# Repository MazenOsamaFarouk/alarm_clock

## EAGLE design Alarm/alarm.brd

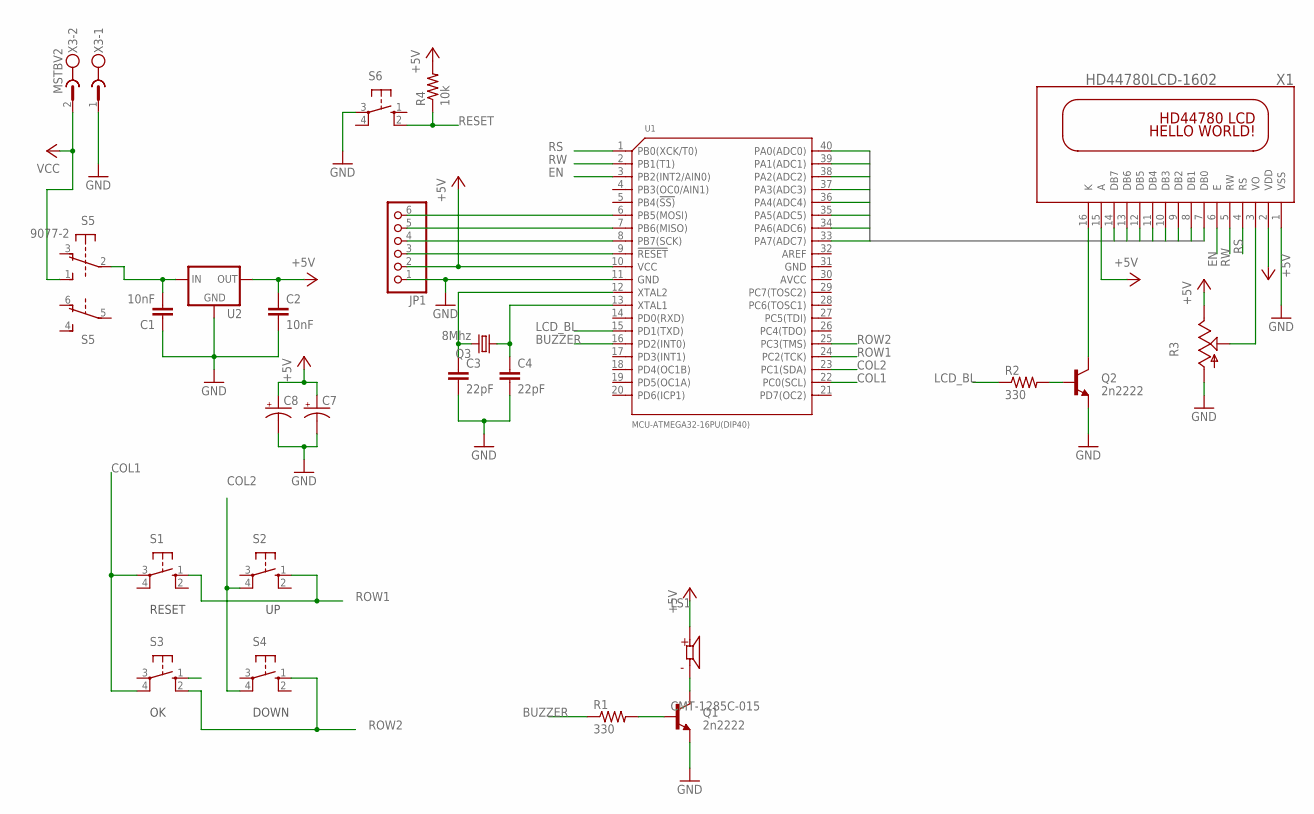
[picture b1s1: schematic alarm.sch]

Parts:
C1, C2: 10nF; C025-025X050
C3, C4: 22pF; C025-025X050
C7, C8: CPOL-USE2.5-6; E2,5-6
JP1: PINHD-1X6; 1X06
LS1: CMT-1285C-015; CUI_CMT-1285C-015
Q1, Q2: 2n2222; TO-92
Q3: 8Mhz; HC49/S
R1, R2: 330; 0207/10
R3: TRIM_US-RS3; RS3
R4: 10k; 0207/10
S1, S2, S3, S4, S6: 10-XX; B3F-10XX
S5: 9077-2
U1: MCU-ATMEGA32-16PU(DIP40); DIP40-2.54-52.3X15.24MM
U2: 78XXL
X1: HD44780LCD-1602; LCD1602
X3: MSTBV2

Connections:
+5V: C2.1, C7.+, C8.+, JP1.2, LS1.P, R3.E, R4.2, U1.10 (VCC), U2.OUT, X1.2 (VDD), X1.15 (A)
BUZZER: R1.1, U1.16 (PD2(INT0))
COL1: S1.3, S3.4 (P1), U1.22 (PC0(SCL))
COL2: S2.4 (P1), S4.4 (P1), U1.23 (PC1(SDA))
EN: U1.3 (PB2(INT2/AIN0)), X1.6 (E)
GND: C1.1, C2.2, C3.2, C4.2, C7.-, C8.-, JP1.1, Q1.3 (E), Q2.3 (E), R3.A, S6.3, U1.11 (GND), U2.GND, X1.1 (VSS), X3.1
LCD_BL: R2.1, U1.15 (PD1(TXD))
unnamed: C1.2, S5.2, U2.IN
unnamed: Q1.2 (B), R1.2
unnamed: LS1.N, Q1.1 (C)
unnamed: C3.1, Q3.2, U1.12 (XTAL2)
unnamed: C4.1, Q3.1, U1.13 (XTAL1)
unnamed: JP1.4, U1.8 (PB7(SCK))
unnamed: JP1.5, U1.7 (PB6(MISO))
unnamed: JP1.6, U1.6 (PB5(MOSI))
unnamed: Q2.1 (C), X1.16 (K)
unnamed: Q2.2 (B), R2.2
unnamed: R3.S, X1.3 (VO)
PA0: U1.40 (PA0(ADC0)), X1.7 (DB0)
PA1: U1.39 (PA1(ADC1)), X1.8 (DB1)
PA2: U1.38 (PA2(ADC2)), X1.9 (DB2)
PA3: U1.37 (PA3(ADC3)), X1.10 (DB3)
PA4: U1.36 (PA4(ADC4)), X1.11 (DB4)
PA5: U1.35 (PA5(ADC5)), X1.12 (DB5)
PA6: U1.34 (PA6(ADC6)), X1.13 (DB6)
PA7: U1.33 (PA7(ADC7)), X1.14 (DB7)
RESET: JP1.3, R4.1, S6.2 (S1), U1.9 (!RESET)
ROW1: S1.1 (S), S2.1 (S), U1.24 (PC2(TCK))
ROW2: S3.2 (S1), S4.1 (S), U1.25 (PC3(TMS))
RS: U1.1 (PB0(XCK/T0)), X1.4 (RS)
RW: U1.2 (PB1(T1)), X1.5 (RW)
VCC: S5.1 (S), X3.2

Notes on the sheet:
RESET
DOWN

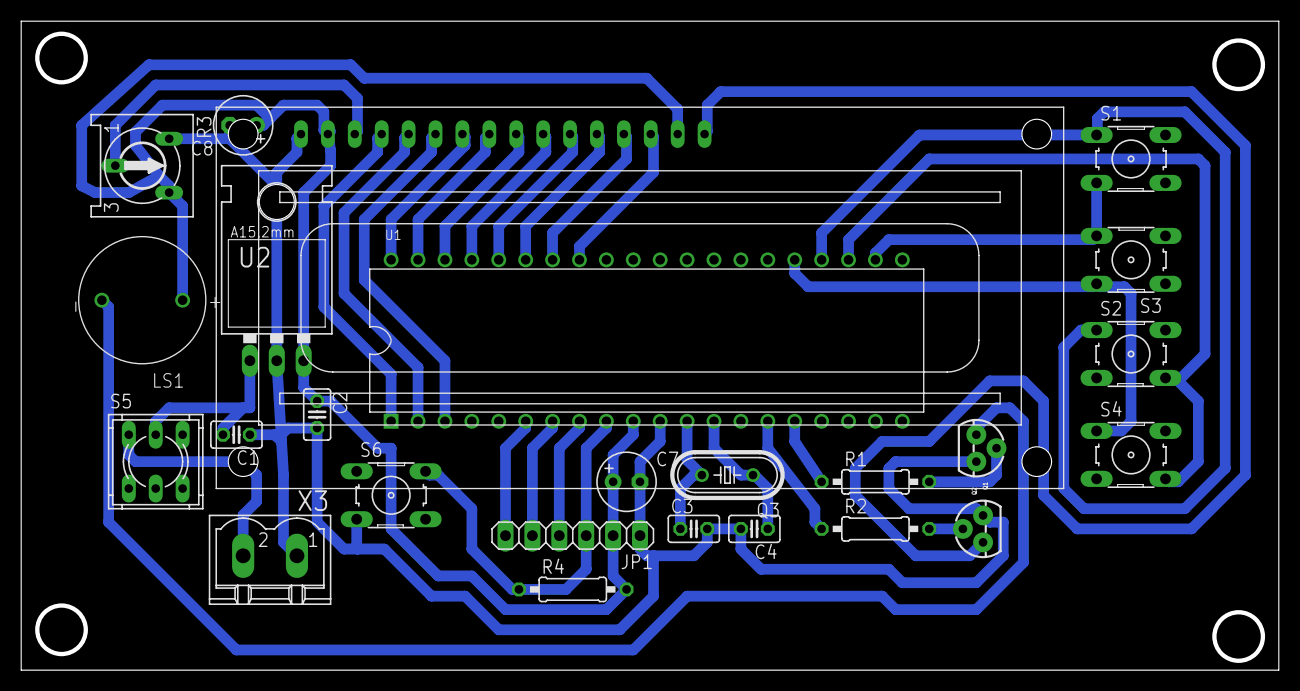
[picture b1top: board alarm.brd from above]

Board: 2 copper layers, 118.7 x 61.3 mm, 25 parts (0 on the bottom side), 32 nets.

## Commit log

2021-03-20 created git repo for the project
2021-03-20 removed old timers library
2021-03-20 added new timers library
2021-03-20 main application structure and includes
2021-03-20 small edits for Timer2
2021-03-20 git ignore
2021-03-20 removed cursor blink
2021-03-20 WARNING: changes made for ATmega16 in ISR __vector_
2021-03-21 added Keypad library instead of buttons
2021-03-21 changed config of LCD to portB and PORTA
2021-03-22 minor edits in timers
2021-03-25 added alarm clock pcb files
2021-03-25 added LCD display on/off control macros
2021-03-25 final commit to main
2021-03-25 eclipse project file changes
2023-01-11 added osama to name
2023-01-11 branch test_8 added its comment in main.c
2023-01-11 branch test_10 added its comment in main.c
2023-01-11 branch test_5 added its comment in main.c
2023-01-11 branch test_2 added its comment in main.c
2023-01-11 branch test_9 added its comment in main.c
2023-01-11 branch test_3 added its comment in main.c
2023-01-11 branch test_6 added its comment in main.c
2023-01-11 branch test_1 added its comment in main.c
2023-01-11 branch test_7 added its comment in main.c
2023-01-11 branch test_4 added its comment in main.c

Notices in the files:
parts and their libraries:
SparkFun-DiscreteSemi: Licensing: Creative Commons ShareAlike 4.0 International - https://creativecommons.org/licenses/by-sa/4.0
